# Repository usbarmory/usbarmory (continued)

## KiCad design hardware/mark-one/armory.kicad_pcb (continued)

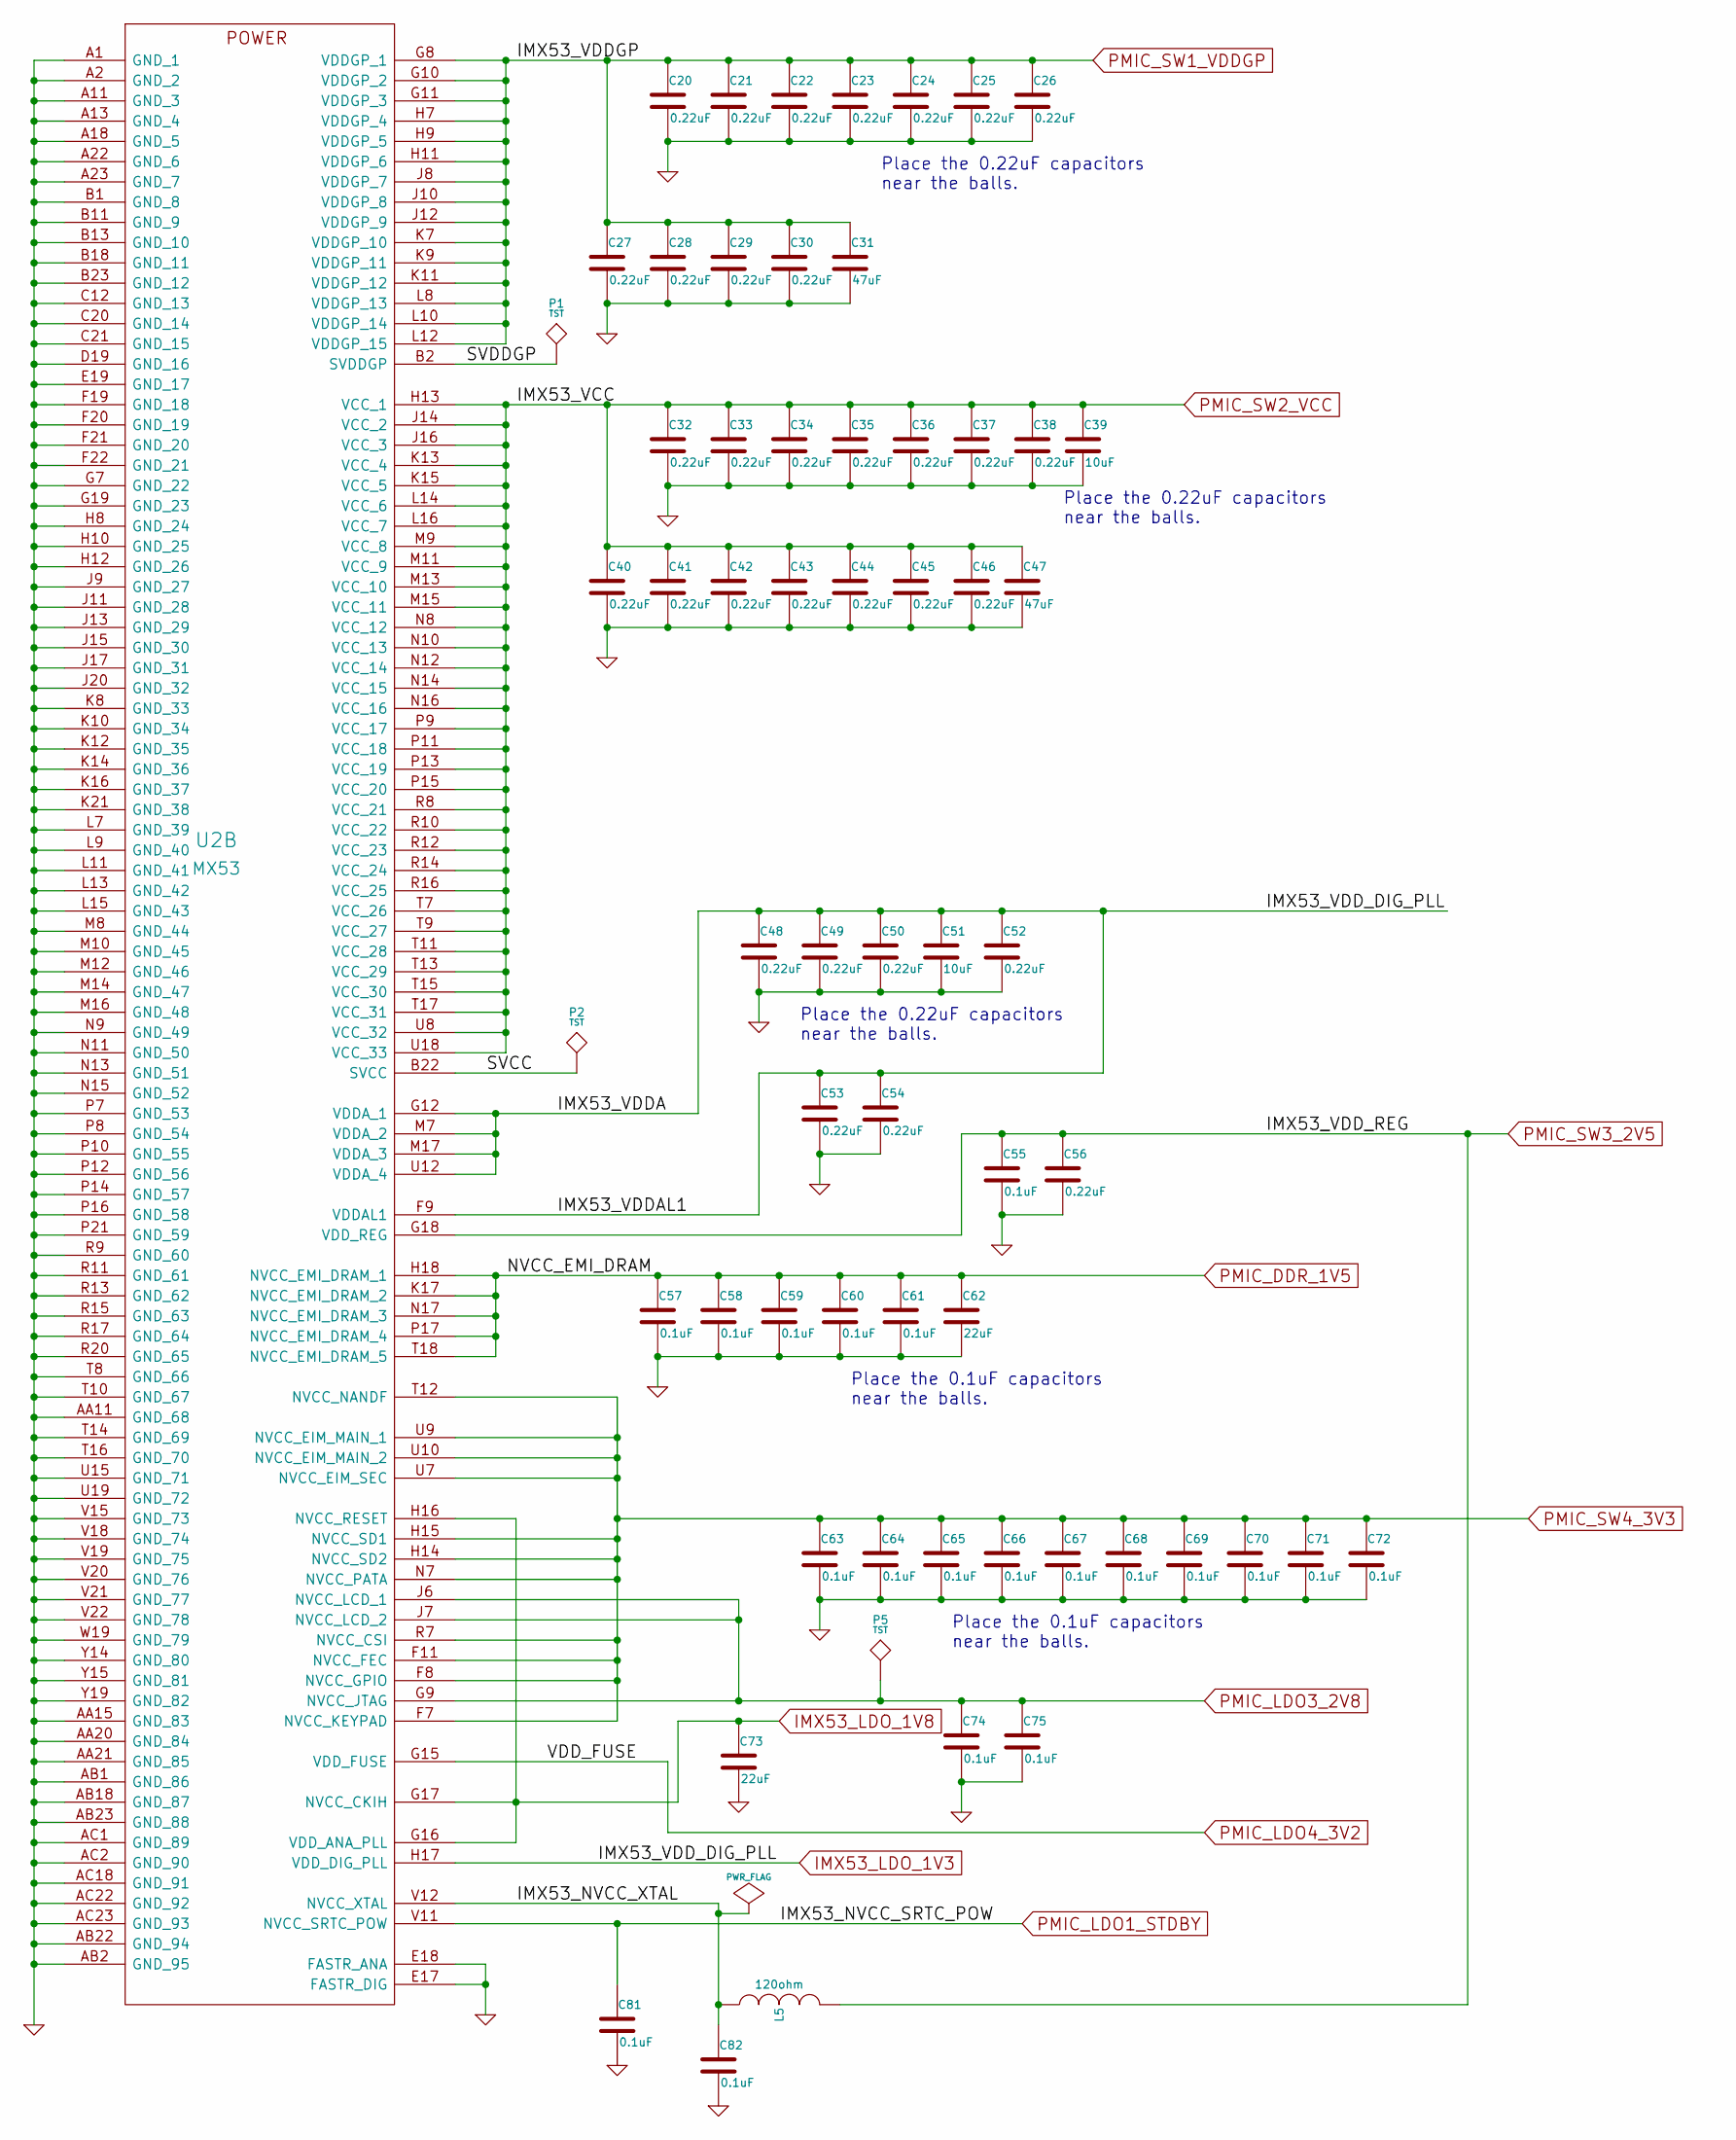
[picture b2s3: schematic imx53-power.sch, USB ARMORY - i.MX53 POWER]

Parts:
C20, C21, C22, C23, C24, C25, C26, C27, C28, C29, C30, C32, C33, C34, C35, C36, C37, C38, C40, C41, C42, C43, C44, C45, C46, C48, C49, C50, C52, C53, C54, C56: 0.22uF; SM0201; Mfg PN C0603X5R0J224M030BB
C31, C47: 47uF; SM0805; Mfg PN C2012X5R0J476M125AC
C39, C51: 10uF; SM0402; Mfg PN C1005X5R0J106M050BC
C55, C57, C58, C59, C60, C61, C63, C64, C65, C66, C67, C68, C69, C70, C71, C72, C74, C75, C81, C82: 0.1uF; SM0201; Mfg PN C0603X5R0J104K030BC
C62, C73: 22uF; SM0603; Mfg PN C1608X5R0J226M080AC
L5: 120ohm; SM0201; Mfg PN 742692003
P1, P2, P5: TST; TP
U2: MX53; Mfg PN MCIMX537CVV8C / MCIMX536AVV8C / MCIMX53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

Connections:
/i.MX53 POWER/IMX53_NVCC_XTAL: C82.1, L5.1, U2.V12 (NVCC_XTAL)
/i.MX53 POWER/SVCC: P2.1, U2.B22 (SVCC)
/i.MX53 POWER/SVDDGP: P1.1, U2.B2 (SVDDGP)
GND: C20.2, C21.2, C22.2, C23.2, C24.2, C25.2, C26.2, C27.2, C28.2, C29.2, C30.2, C31.2, C32.2, C33.2, C34.2, C35.2, C36.2, C37.2, C38.2, C39.2, C40.2, C41.2, C42.2, C43.2, C44.2, C45.2, C46.2, C47.2, C48.2, C49.2, C50.2, C51.2, C52.2, C53.2, C54.2, C55.2, C56.2, C57.2, C58.2, C59.2, C60.2, C61.2, C62.2, C63.2, C64.2, C65.2, C66.2, C67.2, C68.2, C69.2, C70.2, C71.2, C72.2, C73.2, C74.2, C75.2, C81.2, C82.2, U2.A1 (GND_1), U2.A2 (GND_2), U2.A11 (GND_3), U2.A13 (GND_4), U2.A18 (GND_5), U2.A22 (GND_6), U2.A23 (GND_7), U2.AA11 (GND_68), U2.AA15 (GND_83), U2.AA20 (GND_84), U2.AA21 (GND_85), U2.AB1 (GND_86), U2.AB2 (GND_95), U2.AB18 (GND_87), U2.AB22 (GND_94), U2.AB23 (GND_88), U2.AC1 (GND_89), U2.AC2 (GND_90), U2.AC18 (GND_91), U2.AC22 (GND_92), U2.AC23 (GND_93), U2.B1 (GND_8), U2.B11 (GND_9), U2.B13 (GND_10), U2.B18 (GND_11), U2.B23 (GND_12), U2.C12 (GND_13), U2.C20 (GND_14), U2.C21 (GND_15), U2.D19 (GND_16), U2.E17 (FASTR_DIG), U2.E18 (FASTR_ANA), U2.E19 (GND_17), U2.F19 (GND_18), U2.F20 (GND_19), U2.F21 (GND_20), U2.F22 (GND_21), U2.G7 (GND_22), U2.G19 (GND_23), U2.H8 (GND_24), U2.H10 (GND_25), U2.H12 (GND_26), U2.J9 (GND_27), U2.J11 (GND_28), U2.J13 (GND_29), U2.J15 (GND_30), U2.J17 (GND_31), U2.J20 (GND_32), U2.K8 (GND_33), U2.K10 (GND_34), U2.K12 (GND_35), U2.K14 (GND_36), U2.K16 (GND_37), U2.K21 (GND_38), U2.L7 (GND_39), U2.L9 (GND_40), U2.L11 (GND_41), U2.L13 (GND_42), U2.L15 (GND_43), U2.M8 (GND_44), U2.M10 (GND_45), U2.M12 (GND_46), U2.M14 (GND_47), U2.M16 (GND_48), U2.N9 (GND_49), U2.N11 (GND_50), U2.N13 (GND_51), U2.N15 (GND_52), U2.P7 (GND_53), U2.P8 (GND_54), U2.P10 (GND_55), U2.P12 (GND_56), U2.P14 (GND_57), U2.P16 (GND_58), U2.P21 (GND_59), U2.R9 (GND_60), U2.R11 (GND_61), U2.R13 (GND_62), U2.R15 (GND_63), U2.R17 (GND_64), U2.R20 (GND_65), U2.T8 (GND_66), U2.T10 (GND_67), U2.T14 (GND_69), U2.T16 (GND_70), U2.U15 (GND_71), U2.U19 (GND_72), U2.V15 (GND_73), U2.V18 (GND_74), U2.V19 (GND_75), U2.V20 (GND_76), U2.V21 (GND_77), U2.V22 (GND_78), U2.W19 (GND_79), U2.Y14 (GND_80), U2.Y15 (GND_81), U2.Y19 (GND_82); also elsewhere on the board
IMX53_LDO_1V3: C48.1, C49.1, C50.1, C51.1, C52.1, C53.1, C54.1, U2.F9 (VDDAL1), U2.G12 (VDDA_1), U2.H17 (VDD_DIG_PLL), U2.M7 (VDDA_2), U2.M17 (VDDA_3), U2.U12 (VDDA_4)
IMX53_LDO_1V8: C73.1, U2.G16 (VDD_ANA_PLL), U2.G17 (NVCC_CKIH), U2.H16 (NVCC_RESET); also elsewhere on the board
PMIC_DDR_1V5: C57.1, C58.1, C59.1, C60.1, C61.1, C62.1, U2.H18 (NVCC_EMI_DRAM_1), U2.K17 (NVCC_EMI_DRAM_2), U2.N17 (NVCC_EMI_DRAM_3), U2.P17 (NVCC_EMI_DRAM_4), U2.T18 (NVCC_EMI_DRAM_5); also elsewhere on the board
PMIC_LDO1_STDBY: C81.1, U2.V11 (NVCC_SRTC_POW); also elsewhere on the board
PMIC_LDO3_2V8: C74.1, C75.1, P5.1, U2.G9 (NVCC_JTAG), U2.J6 (NVCC_LCD_1), U2.J7 (NVCC_LCD_2); also elsewhere on the board
PMIC_LDO4_3V2: U2.G15 (VDD_FUSE); also elsewhere on the board
PMIC_SW1_VDDGP: C20.1, C21.1, C22.1, C23.1, C24.1, C25.1, C26.1, C27.1, C28.1, C29.1, C30.1, C31.1, U2.G8 (VDDGP_1), U2.G10 (VDDGP_2), U2.G11 (VDDGP_3), U2.H7 (VDDGP_4), U2.H9 (VDDGP_5), U2.H11 (VDDGP_6), U2.J8 (VDDGP_7), U2.J10 (VDDGP_8), U2.J12 (VDDGP_9), U2.K7 (VDDGP_10), U2.K9 (VDDGP_11), U2.K11 (VDDGP_12), U2.L8 (VDDGP_13), U2.L10 (VDDGP_14), U2.L12 (VDDGP_15); also elsewhere on the board
PMIC_SW2_VCC: C32.1, C33.1, C34.1, C35.1, C36.1, C37.1, C38.1, C39.1, C40.1, C41.1, C42.1, C43.1, C44.1, C45.1, C46.1, C47.1, U2.H13 (VCC_1), U2.J14 (VCC_2), U2.J16 (VCC_3), U2.K13 (VCC_4), U2.K15 (VCC_5), U2.L14 (VCC_6), U2.L16 (VCC_7), U2.M9 (VCC_8), U2.M11 (VCC_9), U2.M13 (VCC_10), U2.M15 (VCC_11), U2.N8 (VCC_12), U2.N10 (VCC_13), U2.N12 (VCC_14), U2.N14 (VCC_15), U2.N16 (VCC_16), U2.P9 (VCC_17), U2.P11 (VCC_18), U2.P13 (VCC_19), U2.P15 (VCC_20), U2.R8 (VCC_21), U2.R10 (VCC_22), U2.R12 (VCC_23), U2.R14 (VCC_24), U2.R16 (VCC_25), U2.T7 (VCC_26), U2.T9 (VCC_27), U2.T11 (VCC_28), U2.T13 (VCC_29), U2.T15 (VCC_30), U2.T17 (VCC_31), U2.U8 (VCC_32), U2.U18 (VCC_33); also elsewhere on the board
PMIC_SW3_2V5: C55.1, C56.1, L5.2, U2.G18 (VDD_REG); also elsewhere on the board
PMIC_SW4_3V3: C63.1, C64.1, C65.1, C66.1, C67.1, C68.1, C69.1, C70.1, C71.1, C72.1, U2.F7 (NVCC_KEYPAD), U2.F8 (NVCC_GPIO), U2.F11 (NVCC_FEC), U2.H14 (NVCC_SD2), U2.H15 (NVCC_SD1), U2.N7 (NVCC_PATA), U2.R7 (NVCC_CSI), U2.T12 (NVCC_NANDF), U2.U7 (NVCC_EIM_SEC), U2.U9 (NVCC_EIM_MAIN_1), U2.U10 (NVCC_EIM_MAIN_2); also elsewhere on the board

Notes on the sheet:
Place the 0.22uF capacitors near the balls.
Place the 0.1uF capacitors near the balls.

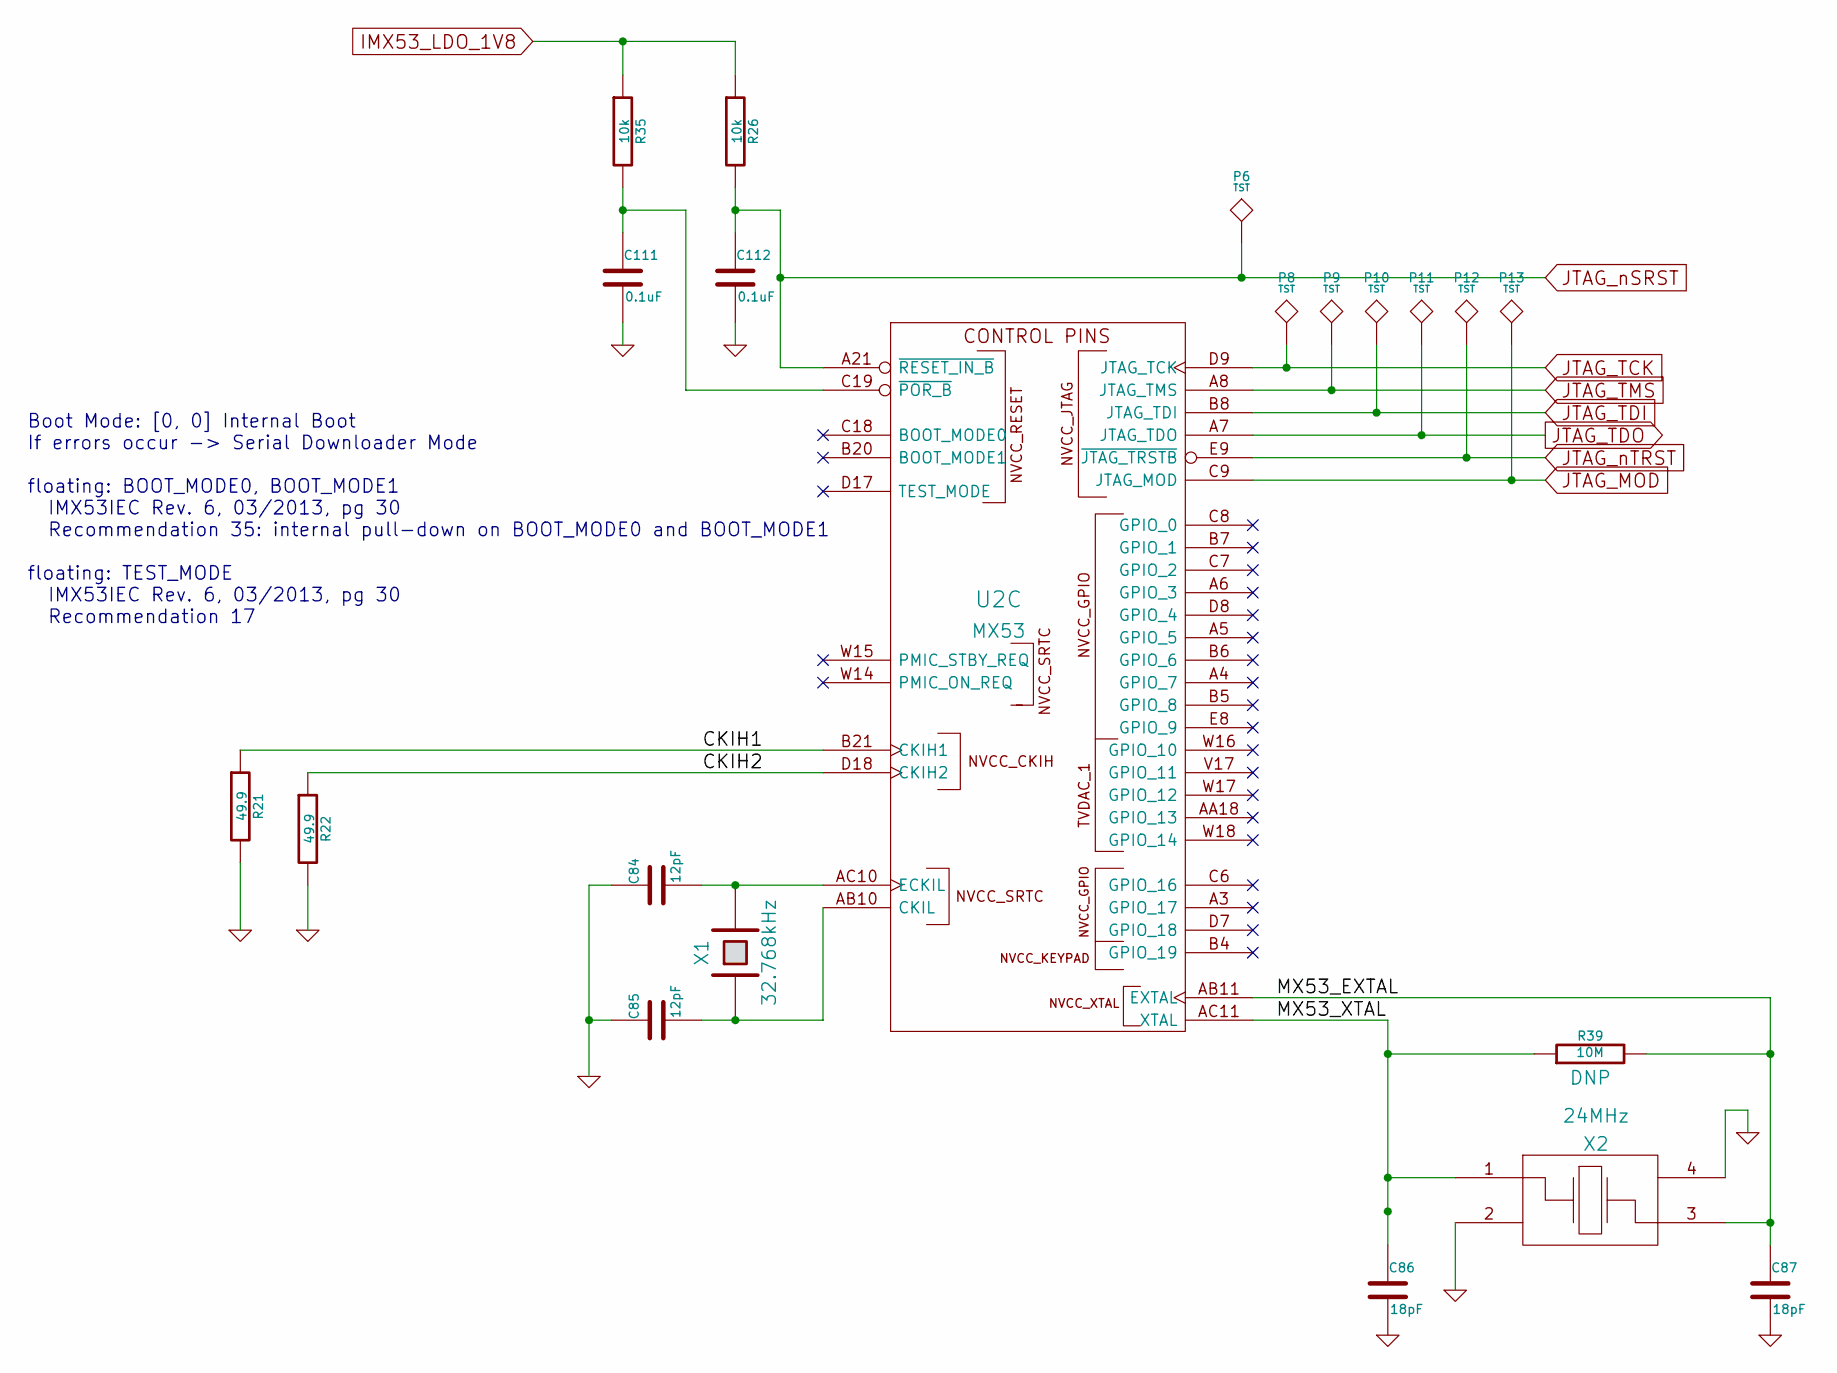
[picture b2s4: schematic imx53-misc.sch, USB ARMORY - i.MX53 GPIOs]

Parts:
C84, C85: 12pF; SM0201; Mfg PN C0603C0G1E120J030BA
C86, C87: 18pF; SM0201; Mfg PN C0603C0G1H180J030BA
C111, C112: 0.1uF; SM0201; Mfg PN C0603X5R0J104K030BC
P6, P8, P9, P10, P11, P12, P13: TST; TP
R21, R22: 49.9; SM0201; Mfg PN CRCW020149R9FNED
R26, R35: 10k; SM0201; Mfg PN CRCW020110K0FNED
R39: 10M; SM0201; Mfg PN CRCW020110M0FNED
U2: MX53
X1: 32.768kHz; CRYSTAL-32k-B; Mfg PN ABS07-32.768KHZ-9-T
X2: 24MHz; CRYSTAL-24M-B; Mfg PN 7M-24.000MEEQ-T

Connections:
/i.MX53 MISC/CKIH1: R21.1, U2.B21 (CKIH1)
/i.MX53 MISC/CKIH2: R22.1, U2.D18 (CKIH2)
/i.MX53 MISC/MX53_EXTAL: C87.1, R39.2, U2.AB11 (EXTAL), X2.3
/i.MX53 MISC/MX53_XTAL: C86.1, R39.1, U2.AC11 (XTAL), X2.1
GND: C84.1, C85.1, C86.2, C87.2, C111.2, C112.2, R21.2, R22.2, X2.2, X2.4; also elsewhere on the board
IMX53_LDO_1V8: R26.1, R35.1; also elsewhere on the board
JTAG_MOD: P13.1, U2.C9 (JTAG_MOD)
JTAG_TCK: P8.1, U2.D9 (JTAG_TCK)
JTAG_TDI: P10.1, U2.B8 (JTAG_TDI)
JTAG_TDO: P11.1, U2.A7 (JTAG_TDO)
JTAG_TMS: P9.1, U2.A8 (JTAG_TMS)
JTAG_nSRST: C112.1, P6.1, R26.2, U2.A21 (~RESET_IN_B)
JTAG_nTRST: P12.1, U2.E9 (~JTAG_TRSTB)
unnamed: C84.2, U2.AC10 (ECKIL), X1.2
unnamed: C85.2, U2.AB10 (CKIL), X1.1
unnamed: C111.1, R35.2, U2.C19 (~POR_B)

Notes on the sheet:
Boot Mode: [0, 0] Internal Boot If errors occur -> Serial Downloader Mode floating: BOOT_MODE0, BOOT_MODE1 IMX53IEC Rev. 6, 03/2013, pg 30 Recommendation 35: internal pull-down on BOOT_MODE0 and BOOT_MODE1 floating: TEST_MODE IMX53IEC Rev. 6, 03/2013, pg 30 Recommendation 17

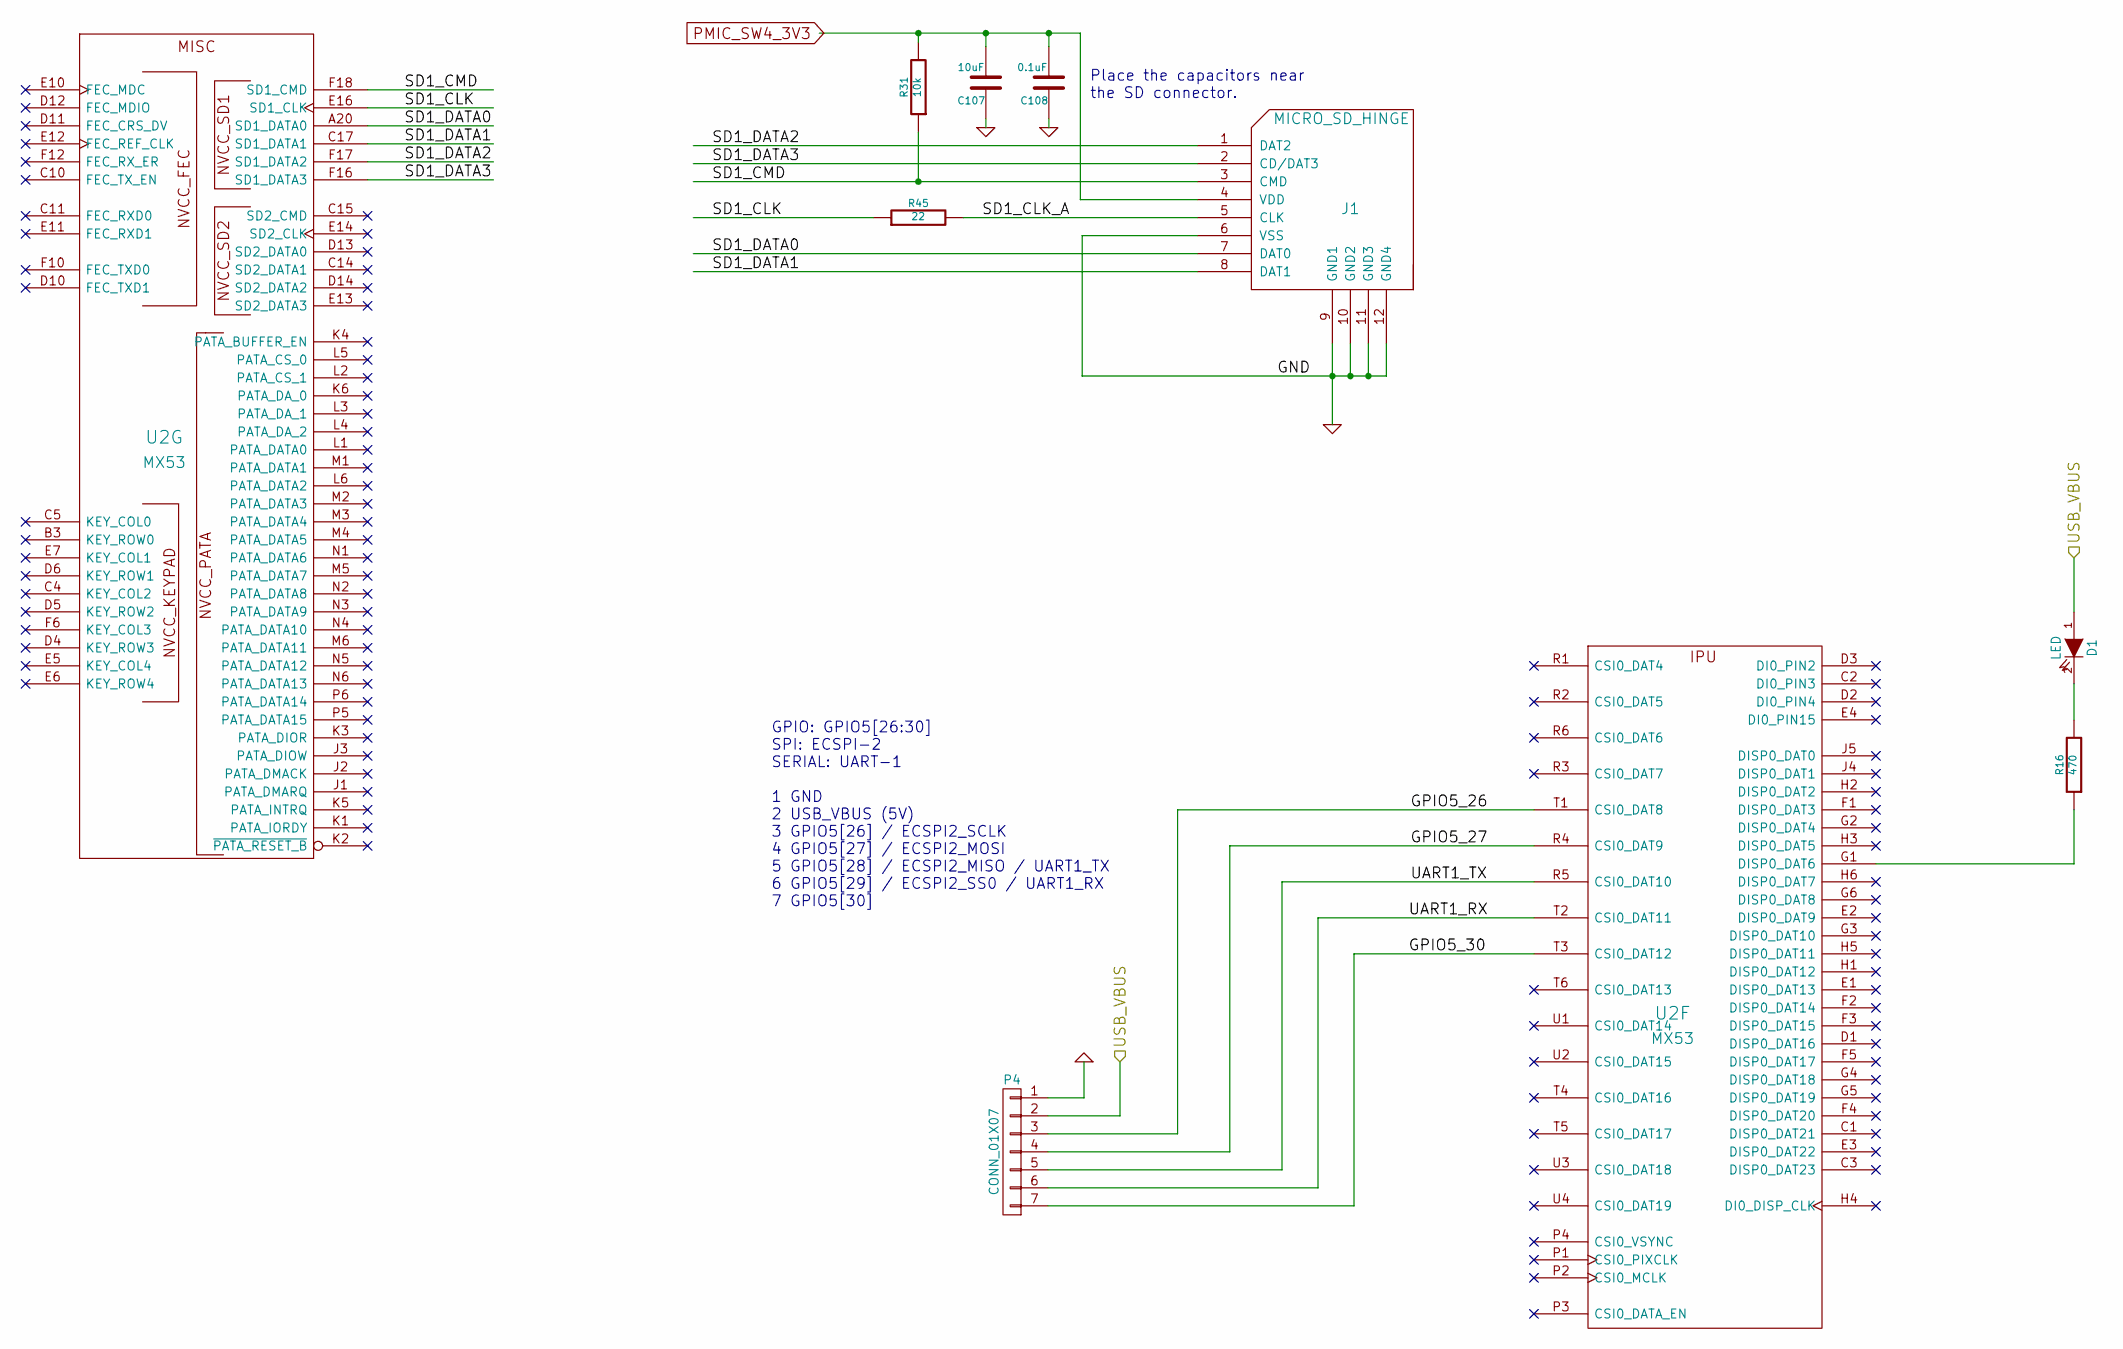
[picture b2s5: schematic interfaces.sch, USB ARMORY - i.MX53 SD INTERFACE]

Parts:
C107: 10uF; SM0603; Mfg PN C1608X5R1A106K080AC
C108: 0.1uF; SM0201; Mfg PN C0603X5R0J104K030BC
D1: LED; SM0603LED; Mfg PN VLMW1300-GS08
J1: MICRO_SD_HINGE; MICRO_SD_HINGE_AMP; Mfg PN 101-00303-68
P4: CONN_01X07; pinhead-1X7
R16: 470; SM0201; Mfg PN CRCW0201470RFNED
R31: 10k; SM0201; Mfg PN CRCW020110K0FNED
R45: 22; SM0201; Mfg PN CRCW020122R0FNED
U2: MX53

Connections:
/Interfaces/GPIO5_26: P4.3, U2.T1 (CSI0_DAT8)
/Interfaces/GPIO5_27: P4.4, U2.R4 (CSI0_DAT9)
/Interfaces/GPIO5_30: P4.7, U2.T3 (CSI0_DAT12)
/Interfaces/SD1_CLK: R45.1, U2.E16 (SD1_CLK)
/Interfaces/SD1_CLK_A: J1.5 (CLK), R45.2
/Interfaces/SD1_CMD: J1.3 (CMD), R31.1, U2.F18 (SD1_CMD)
/Interfaces/SD1_DATA0: J1.7 (DAT0), U2.A20 (SD1_DATA0)
/Interfaces/SD1_DATA1: J1.8 (DAT1), U2.C17 (SD1_DATA1)
/Interfaces/SD1_DATA2: J1.1 (DAT2), U2.F17 (SD1_DATA2)
/Interfaces/SD1_DATA3: J1.2 (CD/DAT3), U2.F16 (SD1_DATA3)
/Interfaces/UART1_RX: P4.6, U2.T2 (CSI0_DAT11)
/Interfaces/UART1_TX: P4.5, U2.R5 (CSI0_DAT10)
/Interfaces/USB_VBUS: D1.1 (A), P4.2; also elsewhere on the board
GND: C107.1, C108.1, J1.6 (VSS), J1.9 (GND1), J1.10 (GND2), J1.11 (GND3), J1.12 (GND4), P4.1; also elsewhere on the board
unnamed: D1.2 (K), R16.2
unnamed: R16.1, U2.G1 (DISP0_DAT6)
PMIC_SW4_3V3: C107.2, C108.2, J1.4 (VDD), R31.2; also elsewhere on the board

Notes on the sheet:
Place the capacitors near the SD connector.
GPIO: GPIO5[26:30] SPI: ECSPI-2 SERIAL: UART-1 1 GND 2 USB_VBUS (5V) 3 GPIO5[26] / ECSPI2_SCLK 4 GPIO5[27] / ECSPI2_MOSI 5 GPIO5[28] / ECSPI2_MISO / UART1_TX 6 GPIO5[29] / ECSPI2_SS0 / UART1_RX 7 GPIO5[30]

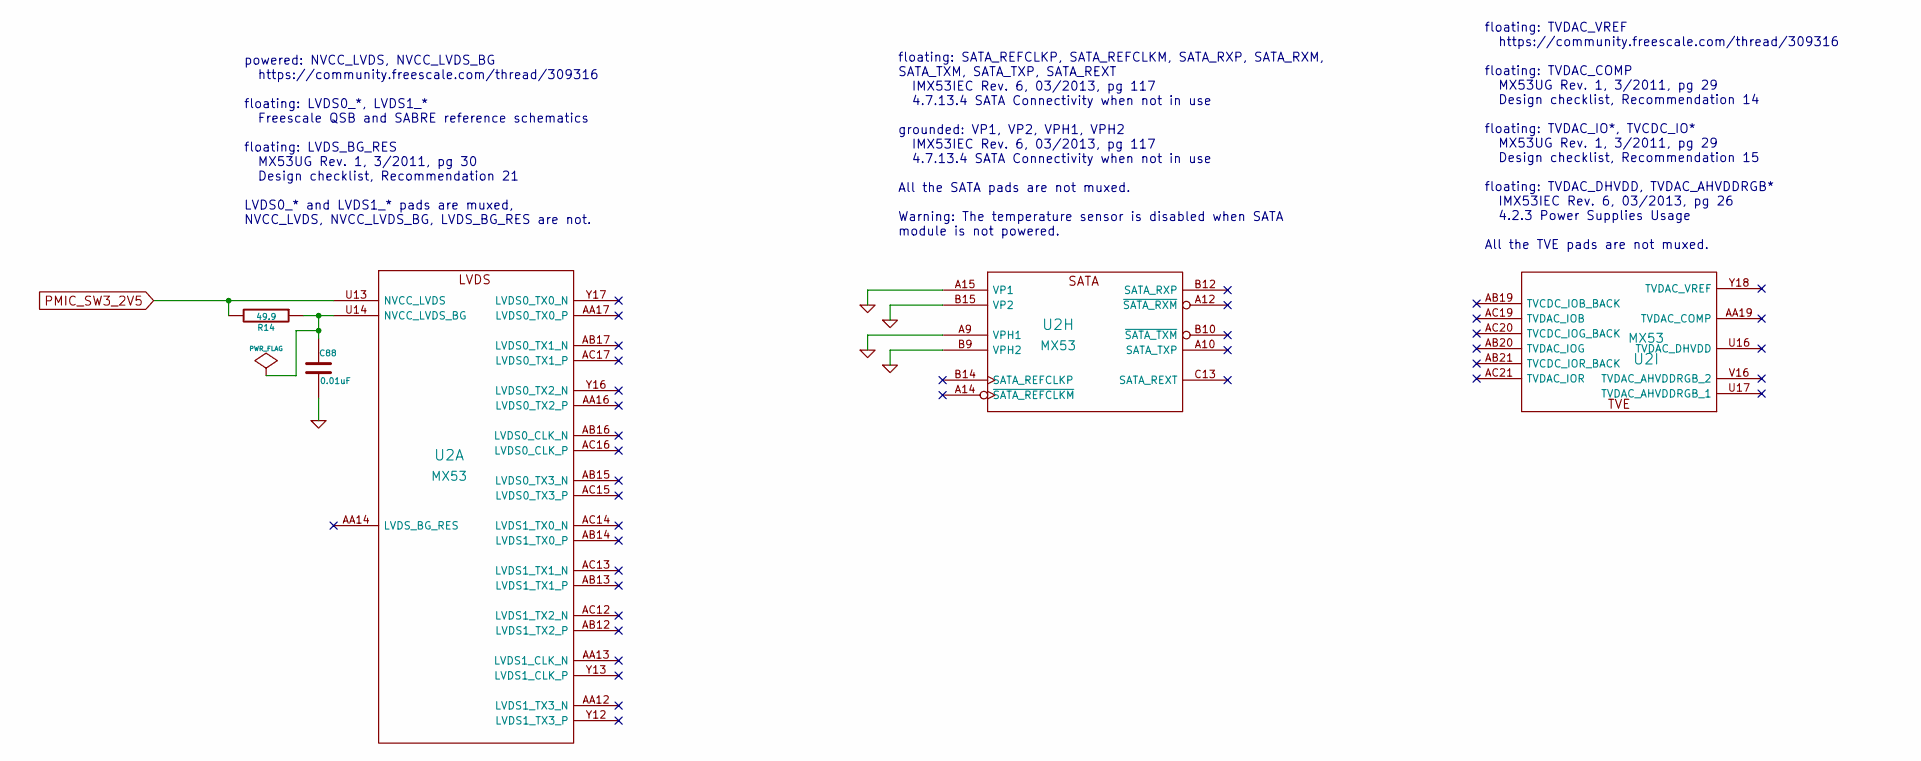
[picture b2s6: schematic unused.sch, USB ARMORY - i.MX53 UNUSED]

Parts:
C88: 0.01uF; SM0201; Mfg PN C0603X7R1A103K030BA
R14: 49.9; SM0201; Mfg PN CRCW020149R9FNED
U2: MX53

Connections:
GND: C88.2, U2.A9 (VPH1), U2.A15 (VP1), U2.B9 (VPH2), U2.B15 (VP2); also elsewhere on the board
unnamed: C88.1, R14.1, U2.U14 (NVCC_LVDS_BG)
PMIC_SW3_2V5: R14.2, U2.U13 (NVCC_LVDS); also elsewhere on the board

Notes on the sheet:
floating: TVDAC_VREF https://community.freescale.com/thread/309316 floating: TVDAC_COMP MX53UG Rev. 1, 3/2011, pg 29 Design checklist, Recommendation 14 floating: TVDAC_IO*, TVCDC_IO* MX53UG Rev. 1, 3/2011, pg 29 Design checklist, Recommendation 15 floating: TVDAC_DHVDD, TVDAC_AHVDDRGB* IMX53IEC Re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
powered: NVCC_LVDS, NVCC_LVDS_BG https://community.freescale.com/thread/309316 floating: LVDS0_*, LVDS1_* Freescale QSB and SABRE reference schematics floating: LVDS_BG_RES MX53UG Rev. 1, 3/2011, pg 30 Design checklist, Recommendation 21 LVDS0_* and LVDS1_* pads are muxed, NVCC_LVDS, NVCC_LVDS_BG, 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
floating: SATA_REFCLKP, SATA_REFCLKM, SATA_RXP, SATA_RXM, SATA_TXM, SATA_TXP, SATA_REXT IMX53IEC Rev. 6, 03/2013, pg 117 4.7.13.4 SATA Connectivity when not in use grounded: VP1, VP2, VPH1, VPH2 IMX53IEC Rev. 6, 03/2013, pg 117 4.7.13.4 SATA Connectivity when not in use All the SATA pads are not mu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

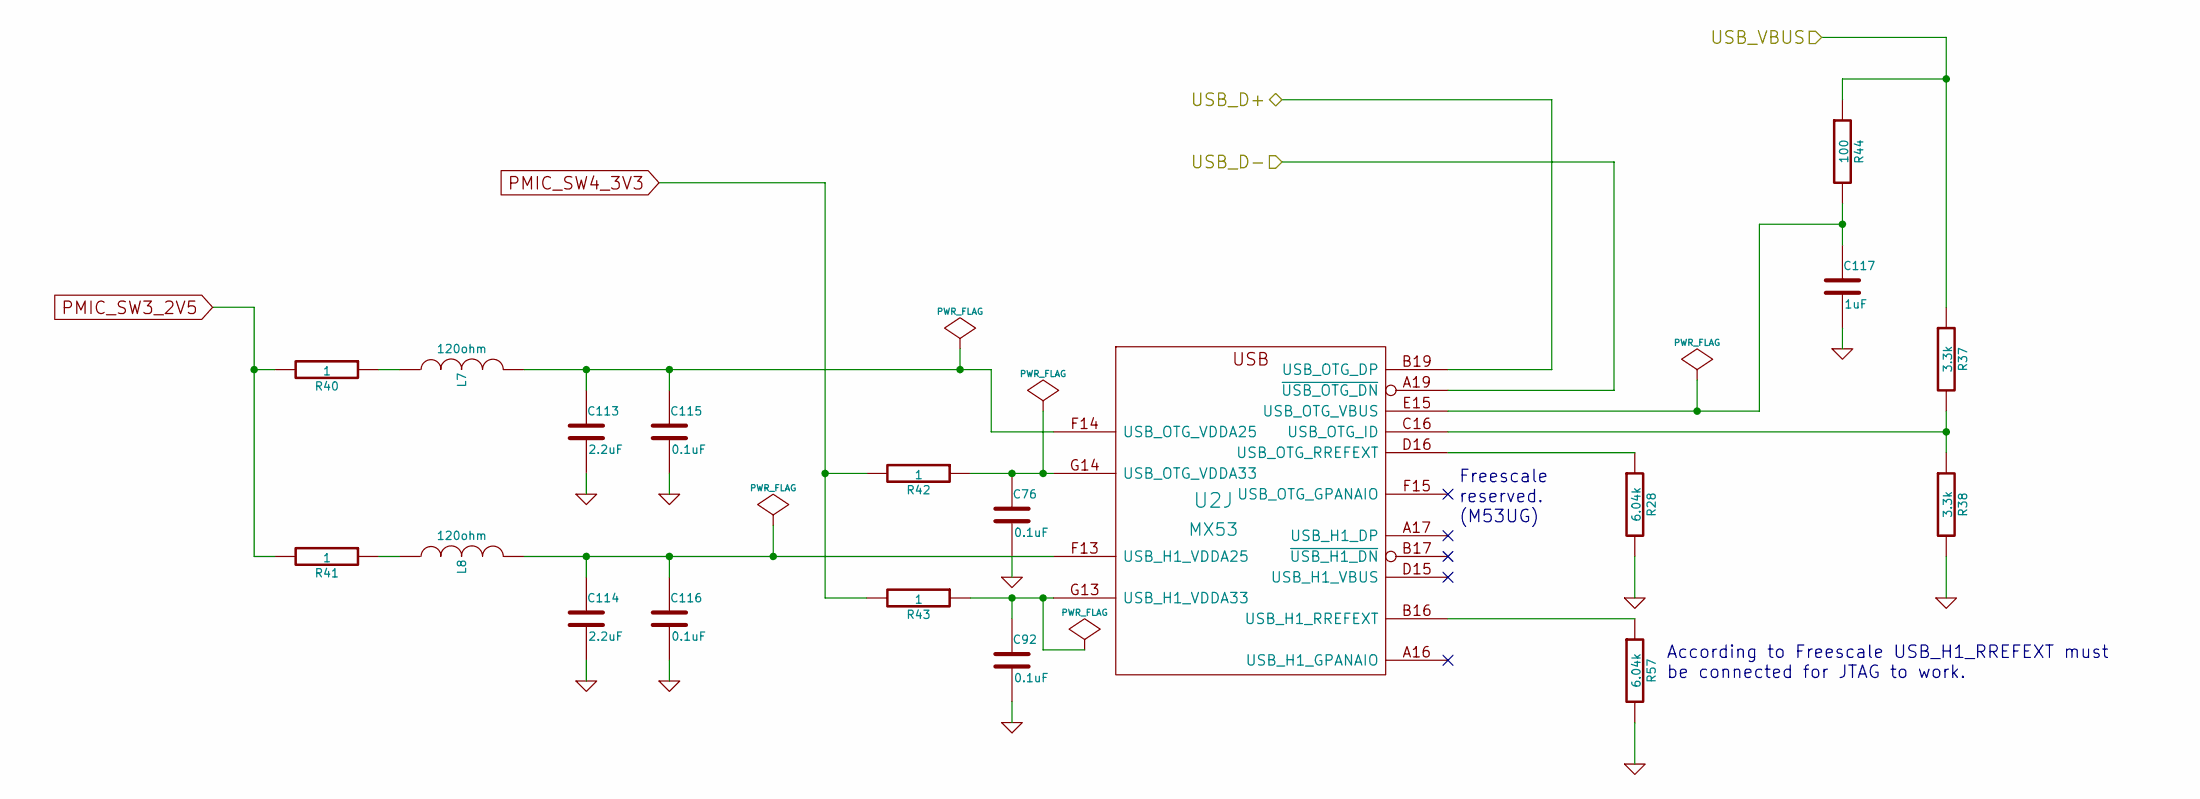
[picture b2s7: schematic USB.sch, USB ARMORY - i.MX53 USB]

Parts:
C76, C92, C115, C116: 0.1uF; SM0201; Mfg PN C0603X5R0J104K030BC
C113, C114: 2.2uF; SM0402; Mfg PN C1005X5R0J225K050BC
C117: 1uF; SM0201; Mfg PN C0603X5R0J105M030BC
L7, L8: 120ohm; SM0201; Mfg PN 742692003
R28, R57: 6.04k; SM0201; Mfg PN CRCW02016K04FNED
R37, R38: 3.3k; SM0201; Mfg PN CRCW02013K30FNED
R40, R41, R42, R43: 1; SM0201; Mfg PN MCRE000220
R44: 100; SM0201; Mfg PN CRCW0201100RFNED
U2: MX53

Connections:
/Interfaces/USB_VBUS: R37.1, R44.1; also elsewhere on the board
/USB/USB_D+: U2.B19 (USB_OTG_DP); also elsewhere on the board
/USB/USB_D-: U2.A19 (~USB_OTG_DN); also elsewhere on the board
GND: C76.2, C92.2, C113.2, C114.2, C115.2, C116.2, C117.2, R28.2, R38.2, R57.2; also elsewhere on the board
unnamed: C76.1, R42.1, U2.G14 (USB_OTG_VDDA33)
unnamed: C92.1, R43.1, U2.G13 (USB_H1_VDDA33)
unnamed: C113.1, C115.1, L7.2, U2.F14 (USB_OTG_VDDA25)
unnamed: C114.1, C116.1, L8.2, U2.F13 (USB_H1_VDDA25)
unnamed: C117.1, R44.2, U2.E15 (USB_OTG_VBUS)
unnamed: L7.1, R40.1
unnamed: L8.1, R41.1
unnamed: R28.1, U2.D16 (USB_OTG_RREFEXT)
unnamed: R37.2, R38.1, U2.C16 (USB_OTG_ID)
unnamed: R57.1, U2.B16 (USB_H1_RREFEXT)
PMIC_SW3_2V5: R40.2, R41.2; also elsewhere on the board
PMIC_SW4_3V3: R42.2, R43.2; also elsewhere on the board

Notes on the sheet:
Freescale reserved. (M53UG)
According to Freescale USB_H1_RREFEXT must be connected for JTAG to work.

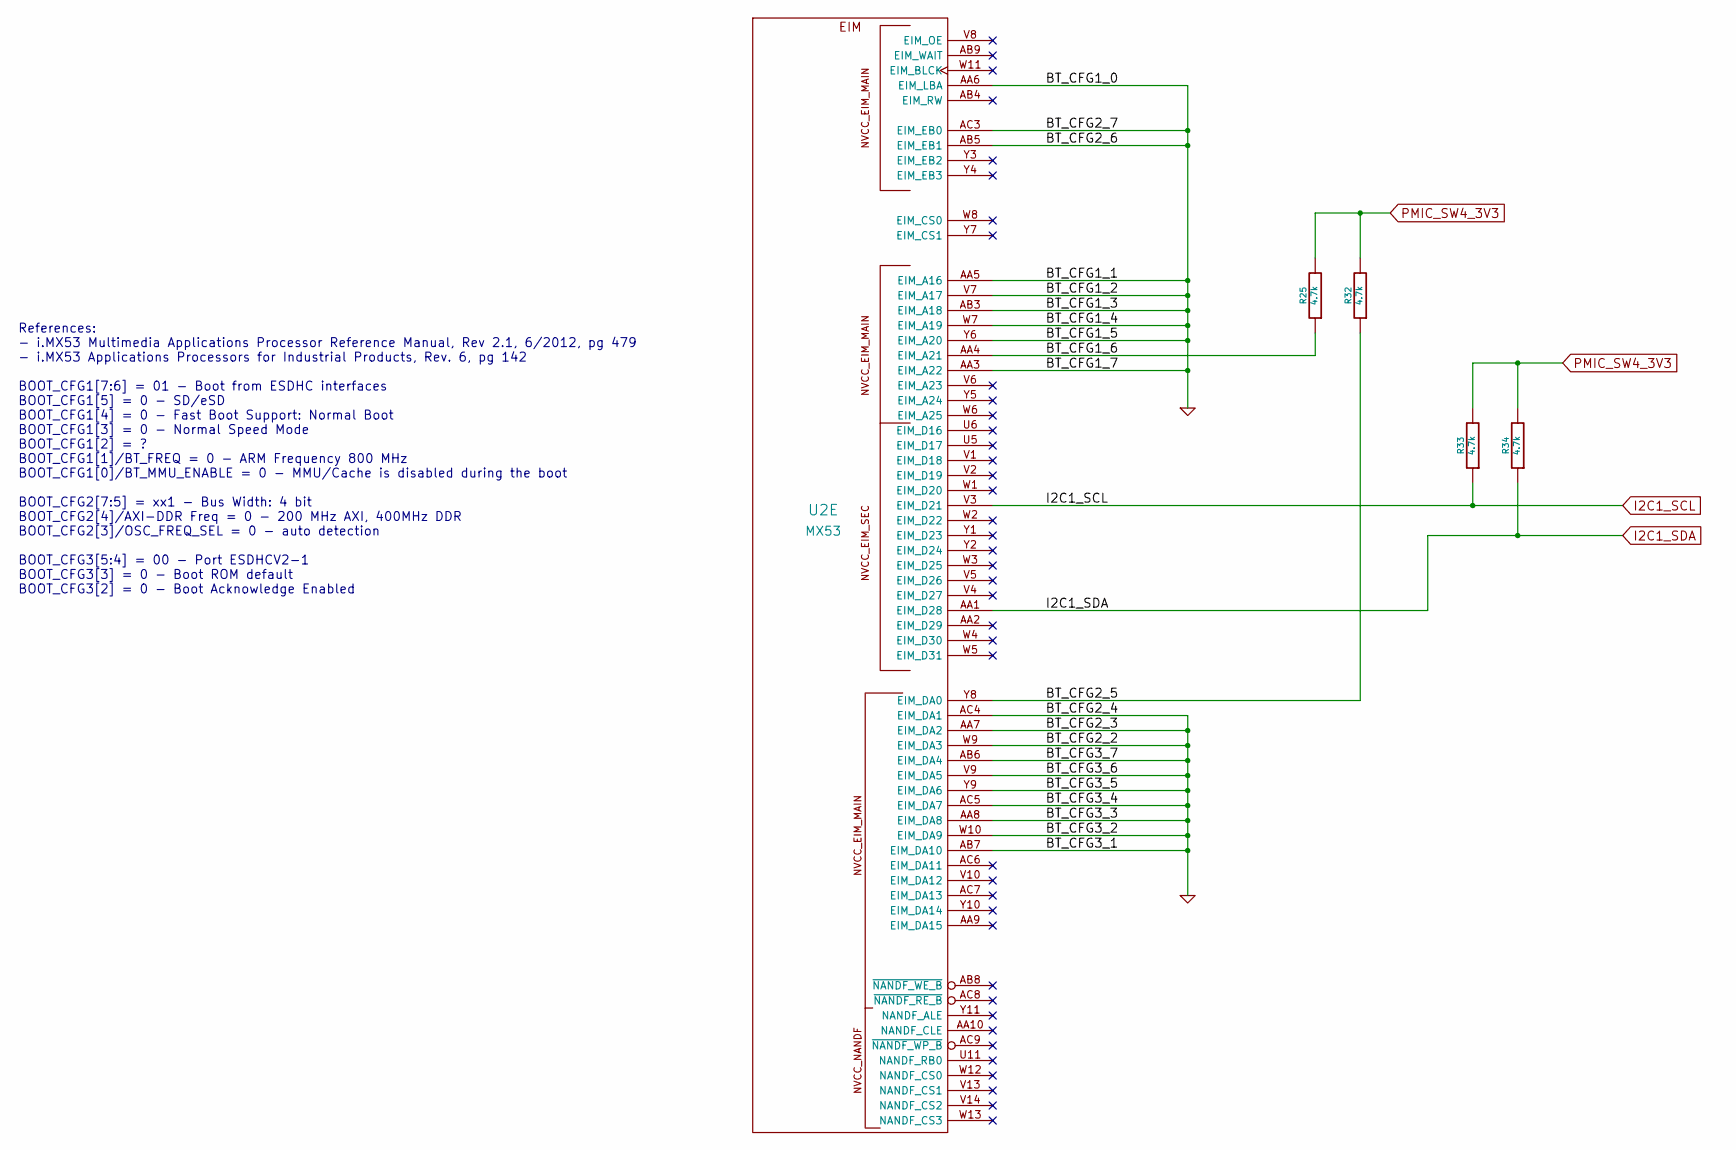
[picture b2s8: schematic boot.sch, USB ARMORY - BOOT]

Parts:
R25, R32, R33, R34: 4.7k; SM0201; Mfg PN CRCW02014K70FNED
U2: MX53

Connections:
/Boot/BT_CFG1_6: R25.1, U2.AA4 (EIM_A21)
/Boot/BT_CFG2_5: R32.1, U2.Y8 (EIM_DA0)
GND: U2.AA3 (EIM_A22), U2.AA5 (EIM_A16), U2.AA6 (EIM_LBA), U2.AA7 (EIM_DA2), U2.AA8 (EIM_DA8), U2.AB3 (EIM_A18), U2.AB5 (EIM_EB1), U2.AB6 (EIM_DA4), U2.AB7 (EIM_DA10), U2.AC3 (EIM_EB0), U2.AC4 (EIM_DA1), U2.AC5 (EIM_DA7), U2.V7 (EIM_A17), U2.V9 (EIM_DA5), U2.W7 (EIM_A19), U2.W9 (EIM_DA3), U2.W10 (EIM_DA9), U2.Y6 (EIM_A20), U2.Y9 (EIM_DA6); also elsewhere on the board
I2C1_SCL: R33.1, U2.V3 (EIM_D21); also elsewhere on the board
I2C1_SDA: R34.1, U2.AA1 (EIM_D28); also elsewhere on the board
PMIC_SW4_3V3: R25.2, R32.2, R33.2, R34.2; also elsewhere on the board

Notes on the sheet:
References: - i.MX53 Multimedia Applications Processor Reference Manual, Rev 2.1, 6/2012, pg 479 - i.MX53 Applications Processors for Industrial Products, Rev. 6, pg 142 BOOT_CFG1[7:6] = 01 - Boot from ESDHC interfaces BOOT_CFG1[5] = 0 - SD/eSD BOOT_CFG1[4] = 0 - Fast Boot Support: Normal Boot BOOT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
